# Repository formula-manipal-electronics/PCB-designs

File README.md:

# PCB-designs
This repository contains all the PCB's designed by the Electronics team for the 2020 season.

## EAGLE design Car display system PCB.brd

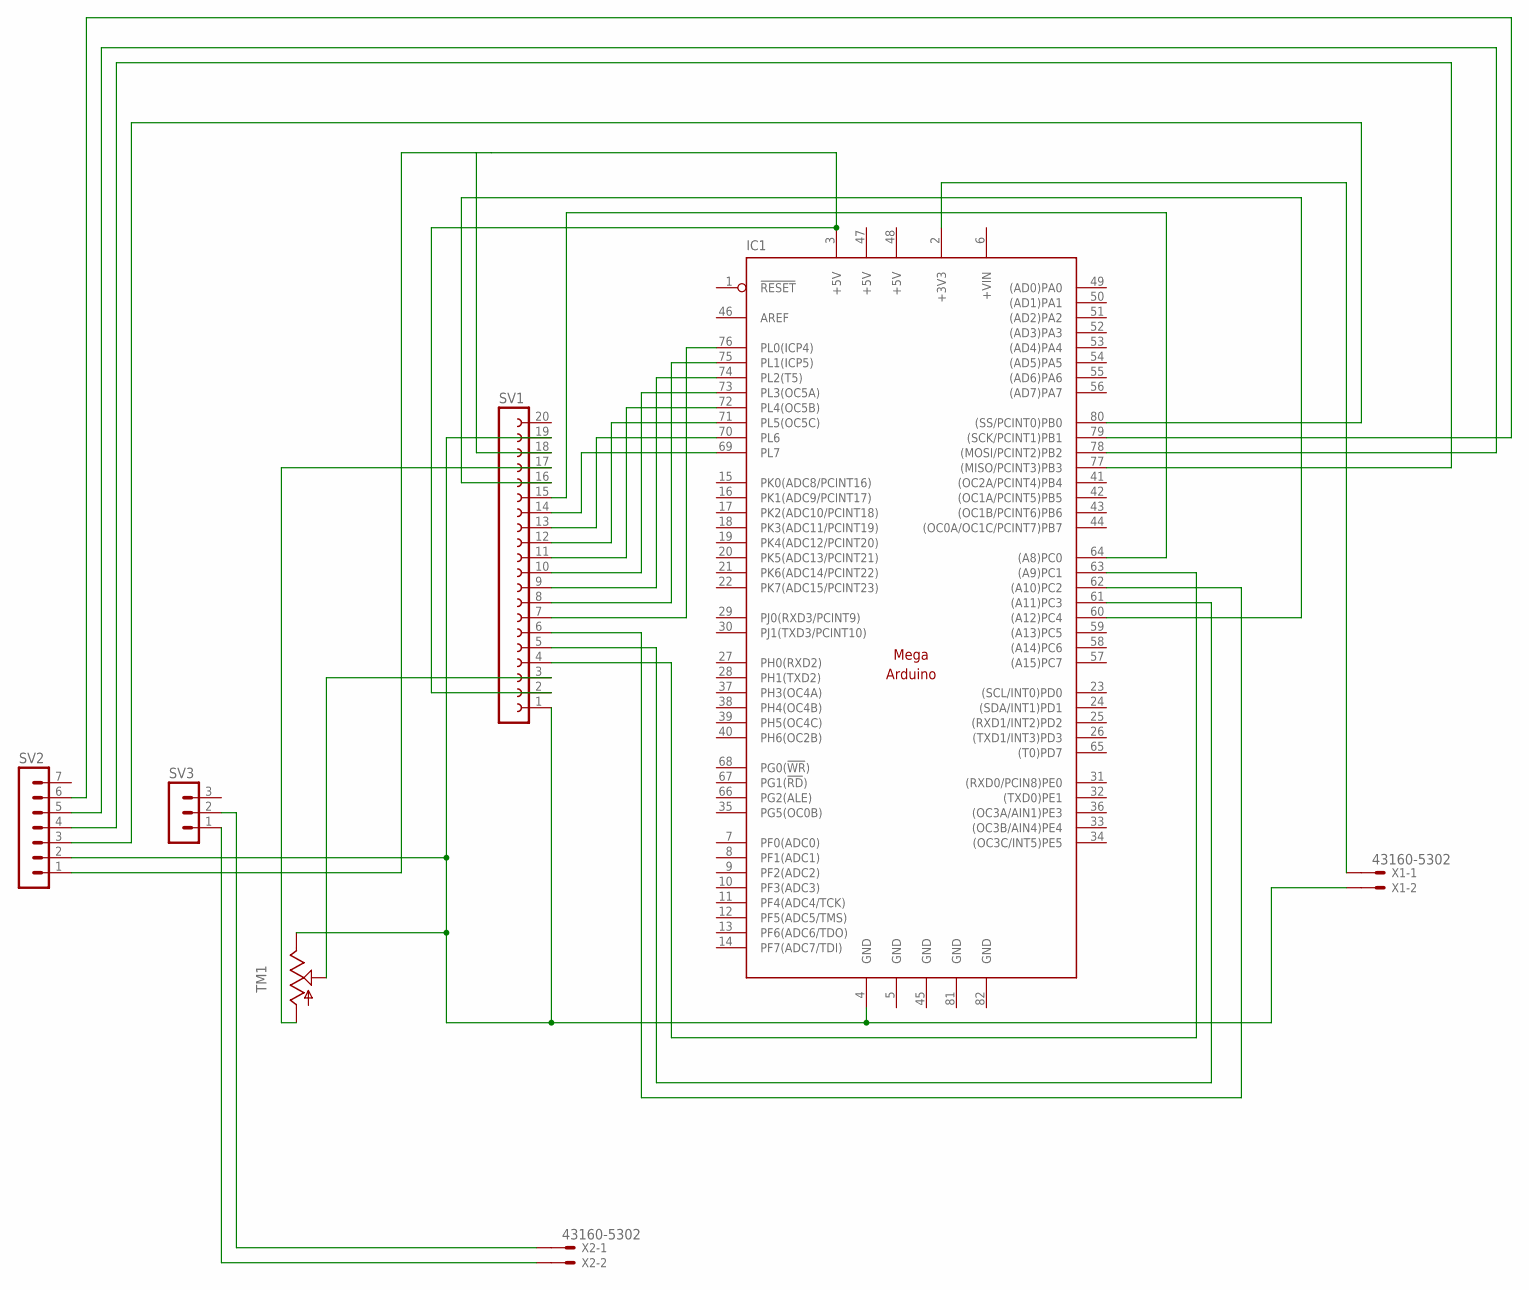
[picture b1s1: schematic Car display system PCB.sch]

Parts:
IC1: MEGAARDUINO_1; MEGA_ARDUINO
SV1: FE20W
SV2: MA07-1
SV3: MA03-1
TM1: TRIM; 6MM
X1, X2: 43160-5302; 43160-XX02

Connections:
+5V: IC1.47 (+5V), IC1.48 (+5V)
+VIN: IC1.6 (+VIN)
GND: IC1.5 (GND), IC1.45 (GND), IC1.81 (GND), IC1.82 (GND)
unnamed: SV1.17, TM1.A
unnamed: IC1.63 ((A9)PC1), SV1.4
unnamed: IC1.61 ((A11)PC3), SV1.5
unnamed: IC1.62 ((A10)PC2), SV1.6
unnamed: IC1.76 (PL0(ICP4)), SV1.7
unnamed: IC1.75 (PL1(ICP5)), SV1.8
unnamed: IC1.74 (PL2(T5)), SV1.9
unnamed: IC1.73 (PL3(OC5A)), SV1.10
unnamed: IC1.72 (PL4(OC5B)), SV1.11
unnamed: IC1.71 (PL5(OC5C)), SV1.12
unnamed: IC1.70 (PL6), SV1.13
unnamed: IC1.69 (PL7), SV1.14
unnamed: IC1.64 ((A8)PC0), SV1.15
unnamed: IC1.60 ((A12)PC4), SV1.16
unnamed: IC1.4 (GND), SV1.1, SV1.19, SV2.2, TM1.E, X1.2@1
unnamed: IC1.3 (+5V), SV1.2, SV1.18, SV2.1
unnamed: IC1.80 ((SS/PCINT0)PB0), SV2.3
unnamed: IC1.77 ((MISO/PCINT3)PB3), SV2.4
unnamed: IC1.78 ((MOSI/PCINT2)PB2), SV2.5
unnamed: IC1.79 ((SCK/PCINT1)PB1), SV2.6
unnamed: SV1.3, TM1.S
unnamed: SV3.1, X2.2@1
unnamed: IC1.2 (+3V3), X1.1@1
unnamed: SV3.2, X2.1@1

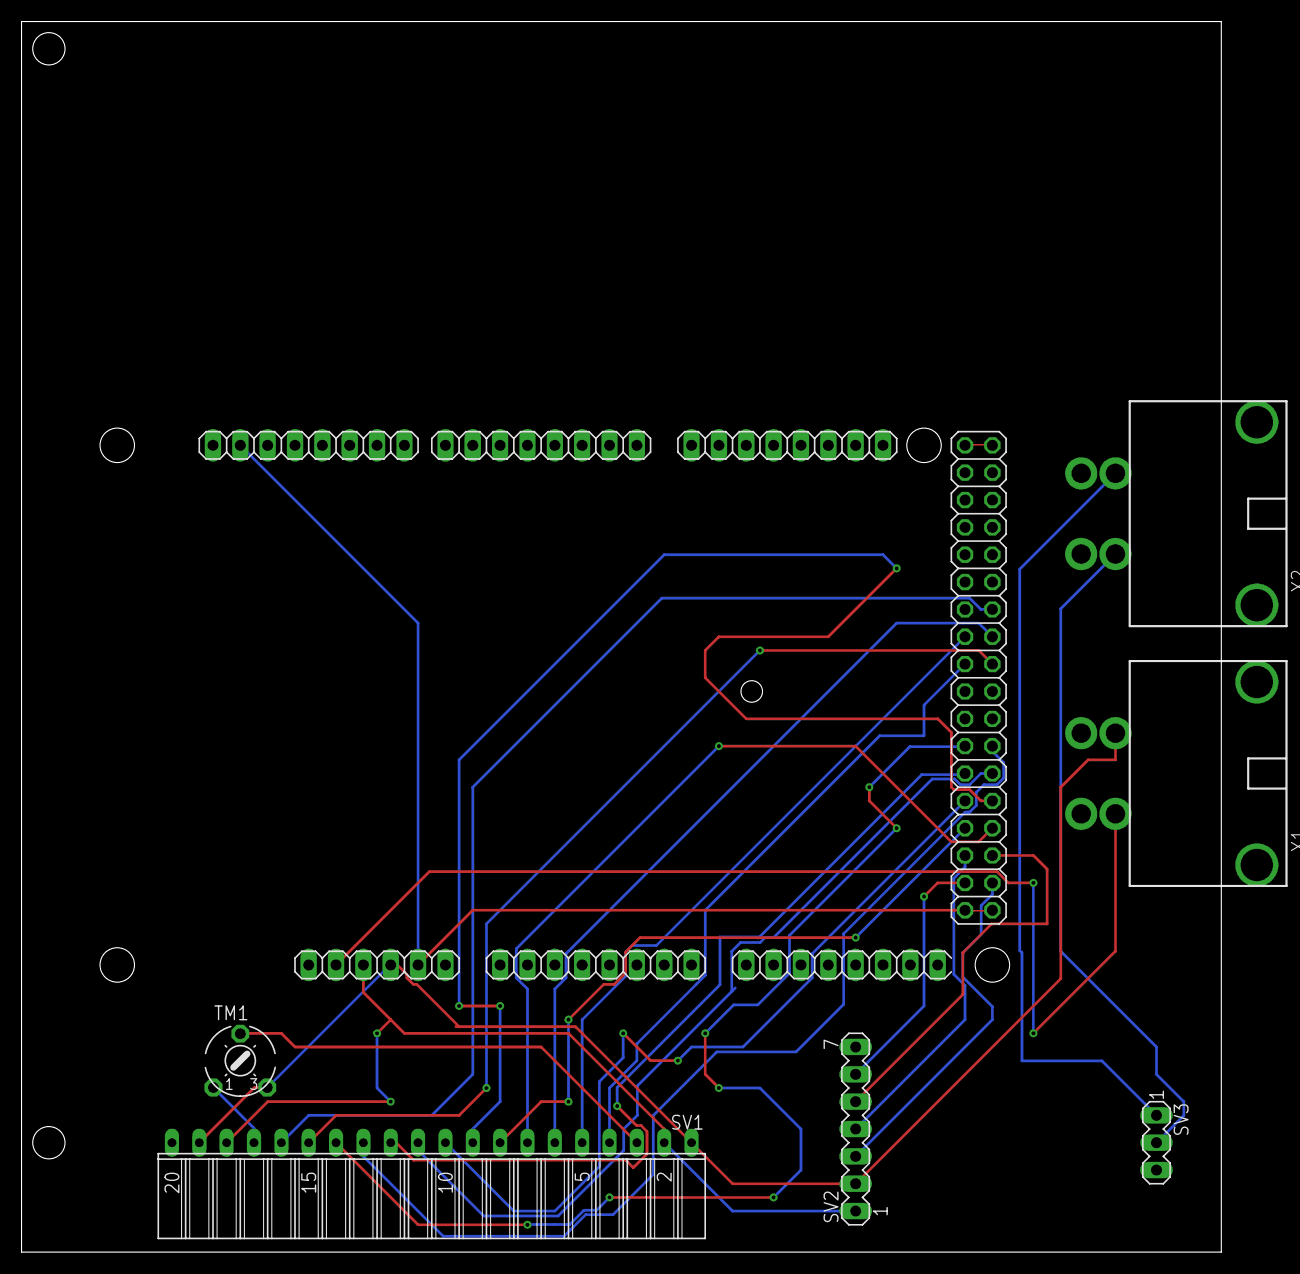
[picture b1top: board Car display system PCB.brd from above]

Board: 2 copper layers, 111.4 x 114.3 mm, 7 parts (0 on the bottom side), 26 nets.

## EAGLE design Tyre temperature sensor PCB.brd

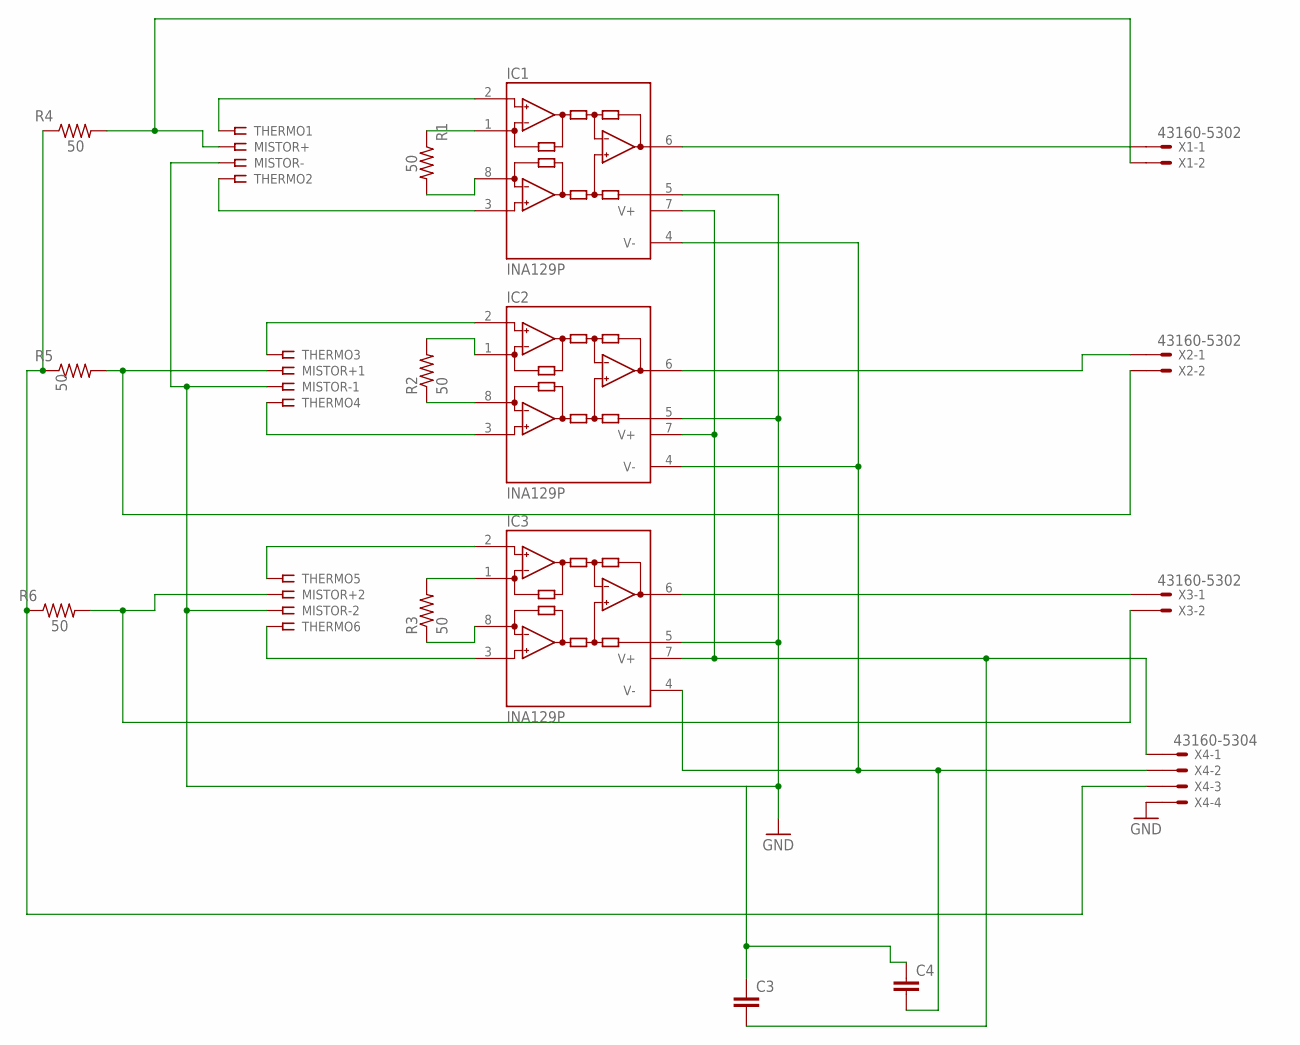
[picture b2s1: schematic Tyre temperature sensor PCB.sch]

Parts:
C3, C4: C5/2.5; C5B2.5
IC1, IC2, IC3: INA129P; DIL08
MISTOR+, MISTOR+1, MISTOR+2: SSW-101-02-G-S
MISTOR-, MISTOR-1, MISTOR-2: SSW-101-02-G-S
R1, R2, R3, R4, R5, R6: 50; 0204/5
THERMO1, THERMO2, THERMO3, THERMO4, THERMO5, THERMO6: SSW-101-02-G-S
X1, X2, X3: 43160-5302; 43160-XX02
X4: 43160-5304; 43160-XX04

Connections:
GND: C3.1, C4.1, IC1.5 (REF), IC2.5 (REF), IC3.5 (REF), MISTOR-.1, MISTOR-1.1, MISTOR-2.1, X4.4@1
unnamed: IC1.1 (RG), R1.1
unnamed: IC1.8 (RG), R1.2
unnamed: IC2.1 (RG), R2.2
unnamed: IC2.8 (RG), R2.1
unnamed: IC3.1 (RG), R3.2
unnamed: IC3.8 (RG), R3.1
unnamed: IC1.3 (+IN), THERMO2.1
unnamed: IC1.2 (-IN), THERMO1.1
unnamed: IC2.3 (+IN), THERMO4.1
unnamed: IC2.2 (-IN), THERMO3.1
unnamed: IC3.3 (+IN), THERMO6.1
unnamed: IC3.2 (-IN), THERMO5.1
unnamed: MISTOR+.1, R4.2, X1.2@1
unnamed: IC1.6 (OUT), X1.1@1
unnamed: IC2.6 (OUT), X2.1@1
unnamed: IC3.6 (OUT), X3.1@1
unnamed: C3.2, IC1.7 (V+), IC2.7 (V+), IC3.7 (V+), X4.1@1
unnamed: C4.2, IC1.4 (V-), IC2.4 (V-), IC3.4 (V-), X4.2@1
unnamed: MISTOR+1.1, R5.2, X2.2@1
unnamed: MISTOR+2.1, R6.2, X3.2@1
unnamed: R4.1, R5.1, R6.1, X4.3@1

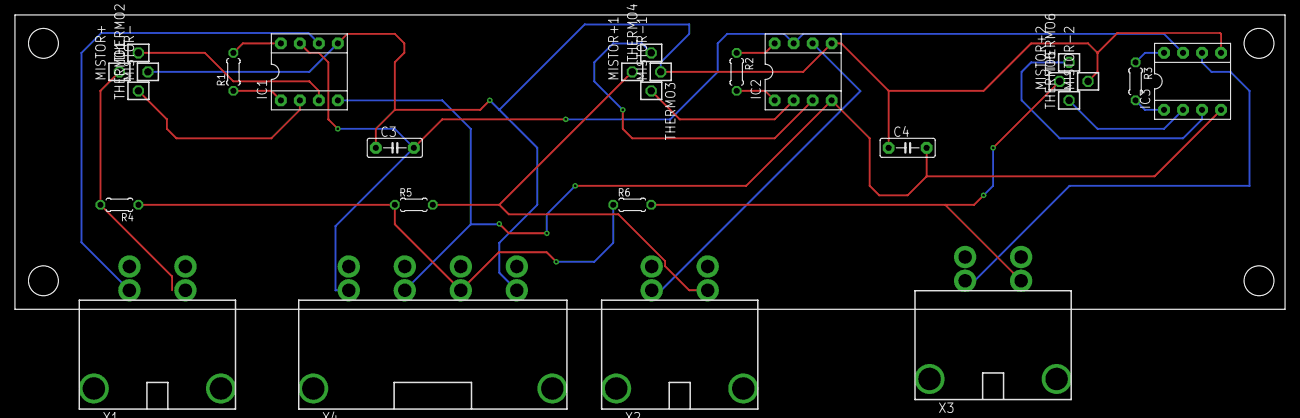
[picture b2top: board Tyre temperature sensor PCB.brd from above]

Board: 2 copper layers, 169.8 x 39.4 mm, 27 parts (0 on the bottom side), 22 nets.

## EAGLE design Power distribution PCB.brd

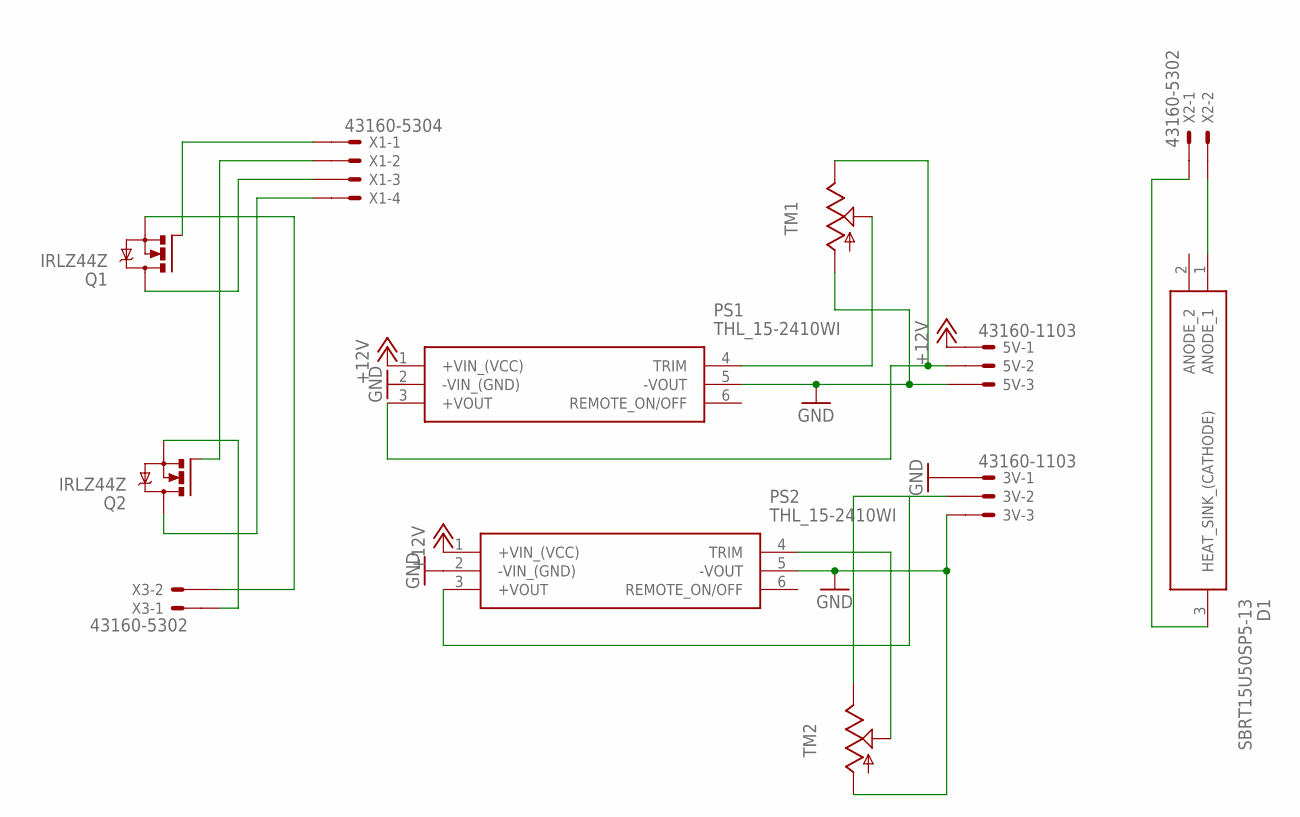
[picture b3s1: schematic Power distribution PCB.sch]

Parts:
3V, 5V: 43160-1103; 43160-XX03
D1: SBRT15U50SP5-13; POWERDI5
PS1, PS2: THL_15-2410WI; THL152410WI
Q1, Q2: IRLZ44Z; TO220BH
TM1, TM2: TRIM; 6MM
X1: 43160-5304; 43160-XX04
X2, X3: 43160-5302; 43160-XX02

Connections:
+12V: 5V.1@1, PS1.1 (+VIN_(VCC)), PS2.1 (+VIN_(VCC))
GND: 3V.1@1, 3V.3@1, 5V.3@1, PS1.5 (-VOUT), PS2.2 (-VIN_(GND)), PS2.5 (-VOUT), TM1.A, TM2.A
unnamed: 5V.2@1, PS1.3 (+VOUT), TM1.E
unnamed: Q1.G, X1.1@1
unnamed: 3V.2@1, PS2.3 (+VOUT), TM2.E
unnamed: Q1.S, X3.2@1
unnamed: PS1.4 (TRIM), TM1.S
unnamed: Q2.S, X3.1@1
unnamed: PS2.4 (TRIM), TM2.S
unnamed: Q2.G, X1.2@1
unnamed: Q1.D, X1.3@1
unnamed: Q2.D, X1.4@1
unnamed: D1.1 (ANODE_1), X2.2@1
unnamed: D1.3 (HEAT_SINK_(CATHODE)), X2.1@1

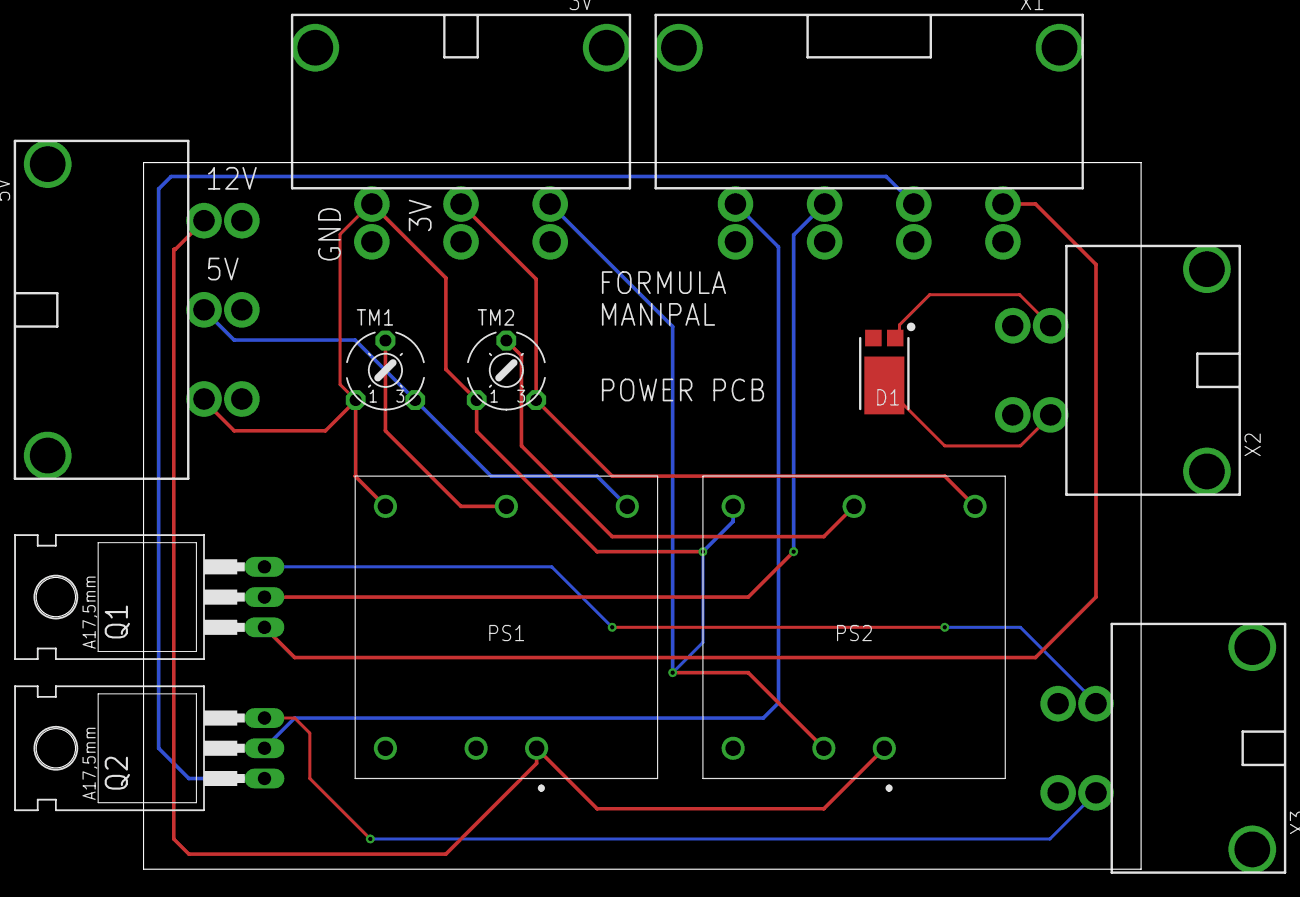
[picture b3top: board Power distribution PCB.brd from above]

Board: 2 copper layers, 83.8 x 59.4 mm, 12 parts (0 on the bottom side), 14 nets.

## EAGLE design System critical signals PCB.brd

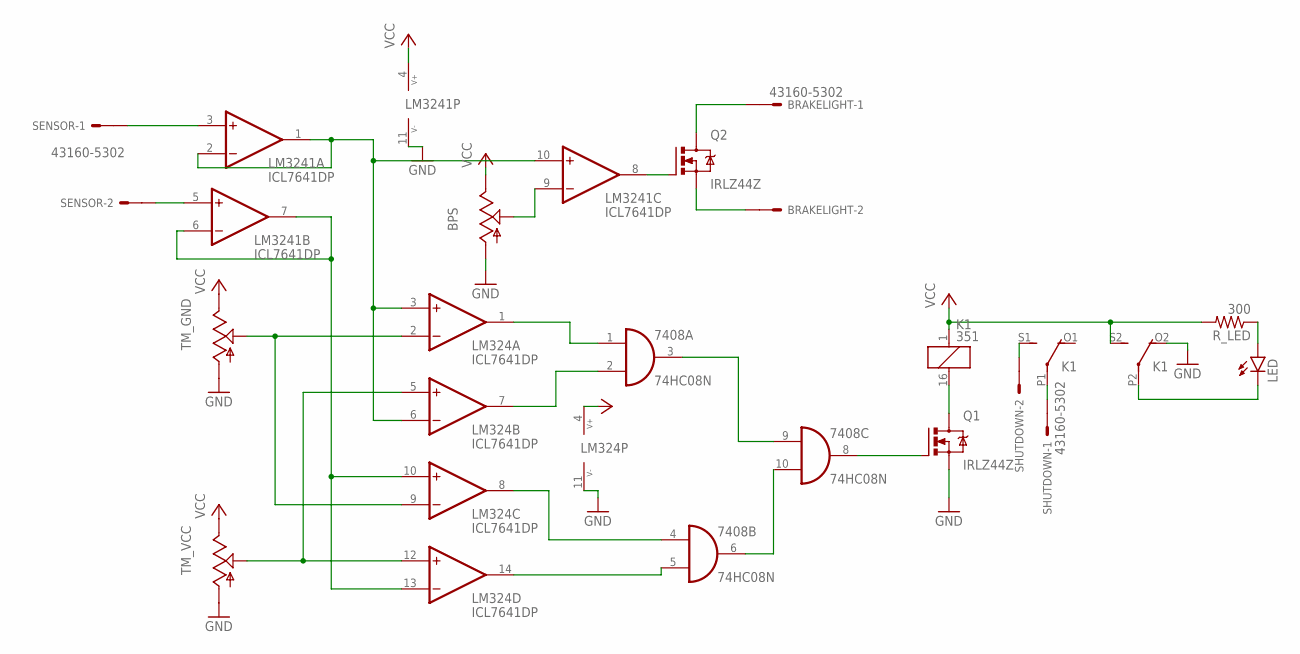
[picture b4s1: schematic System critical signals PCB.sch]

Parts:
7408: 74HC08N; DIL14
BPS: TRIM; 6MM
BRAKELIGHT: 43160-5302; 43160-XX02
K1: 351
LED: LEDCHIP-LED0805; CHIP-LED0805
LM324, LM3241: ICL7641DP; DIL14
Q1, Q2: IRLZ44Z; TO220BH
R_LED: 300; M0805
SENSOR: 43160-5302; 43160-XX02
SHUTDOWN: 43160-5302; 43160-XX02
TM_GND: TRIM; 6MM
TM_VCC: TRIM; 6MM

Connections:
BPS: LM3241.3 (+IN), SENSOR.1@1
GND: 7408.7 (GND), BPS.A, K1.O2 (O), LM324.11 (V-), LM3241.11 (V-), Q1.S, TM_GND.A, TM_VCC.A
unnamed: 7408.4 (I0), LM324.8 (OUT)
unnamed: LM324.3 (+IN), LM324.6 (-IN), LM3241.1 (OUT), LM3241.2 (-IN), LM3241.10 (+IN)
unnamed: LM324.10 (+IN), LM324.13 (-IN), LM3241.6 (-IN), LM3241.7 (OUT)
unnamed: 7408.5 (I1), LM324.14 (OUT)
unnamed: 7408.1 (I0), LM324.1 (OUT)
unnamed: 7408.2 (I1), LM324.7 (OUT)
unnamed: 7408.3 (O), 7408.9 (I0)
unnamed: 7408.6 (O), 7408.10 (I1)
unnamed: 7408.8 (O), Q1.G
unnamed: K1.16 (2), Q1.D
unnamed: K1.S1 (S), SHUTDOWN.2@1
unnamed: K1.P1, SHUTDOWN.1@1
unnamed: LED.A, R_LED.1
unnamed: BPS.S, LM3241.9 (-IN)
unnamed: LM3241.8 (OUT), Q2.G
unnamed: BRAKELIGHT.1@1, Q2.D
unnamed: BRAKELIGHT.2@1, Q2.S
unnamed: K1.P2, LED.C
unnamed: LM324.2 (-IN), LM324.9 (-IN), TM_GND.S
unnamed: LM324.5 (+IN), LM324.12 (+IN), TM_VCC.S
TPS: LM3241.5 (+IN), SENSOR.2@1
VCC: 7408.14 (VCC), BPS.E, K1.1, K1.S2 (S), LM324.4 (V+), LM3241.4 (V+), R_LED.2, TM_GND.E, TM_VCC.E

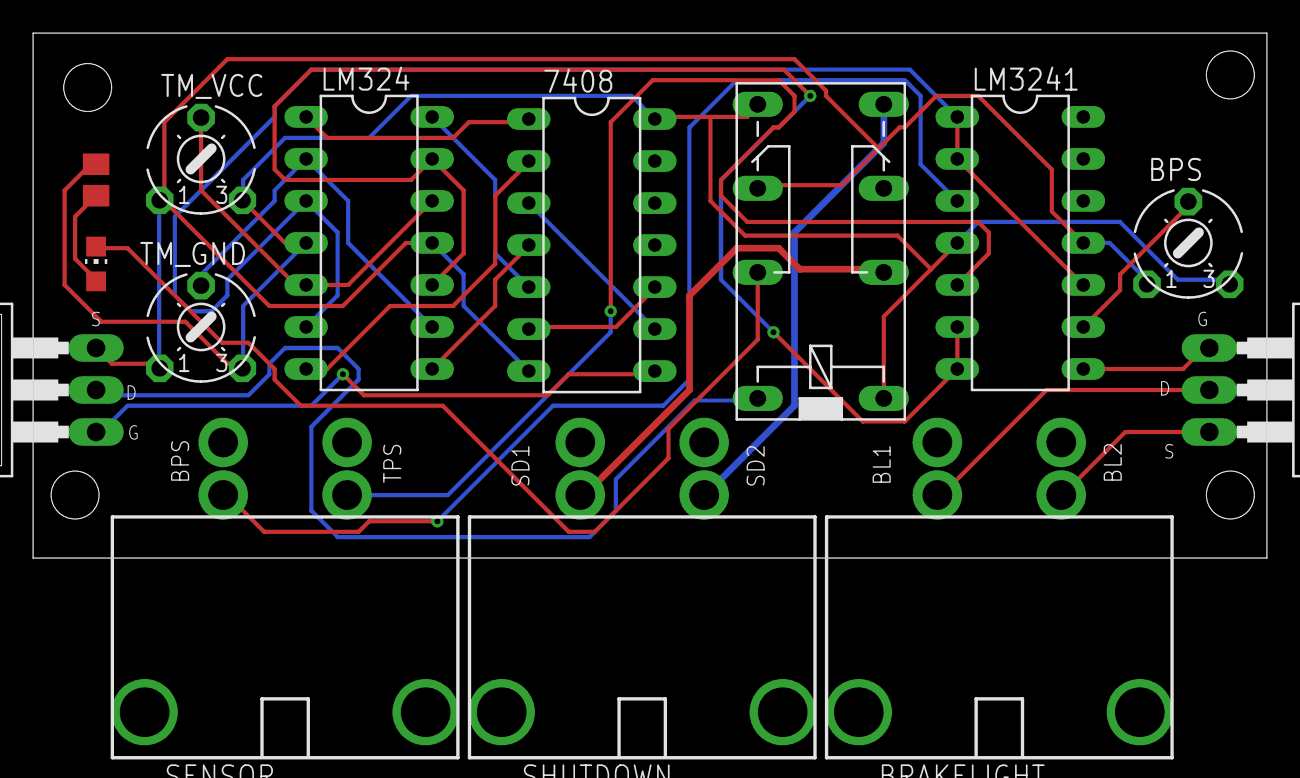
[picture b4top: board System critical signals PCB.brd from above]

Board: 2 copper layers, 74.6 x 31.7 mm, 14 parts (0 on the bottom side), 24 nets.

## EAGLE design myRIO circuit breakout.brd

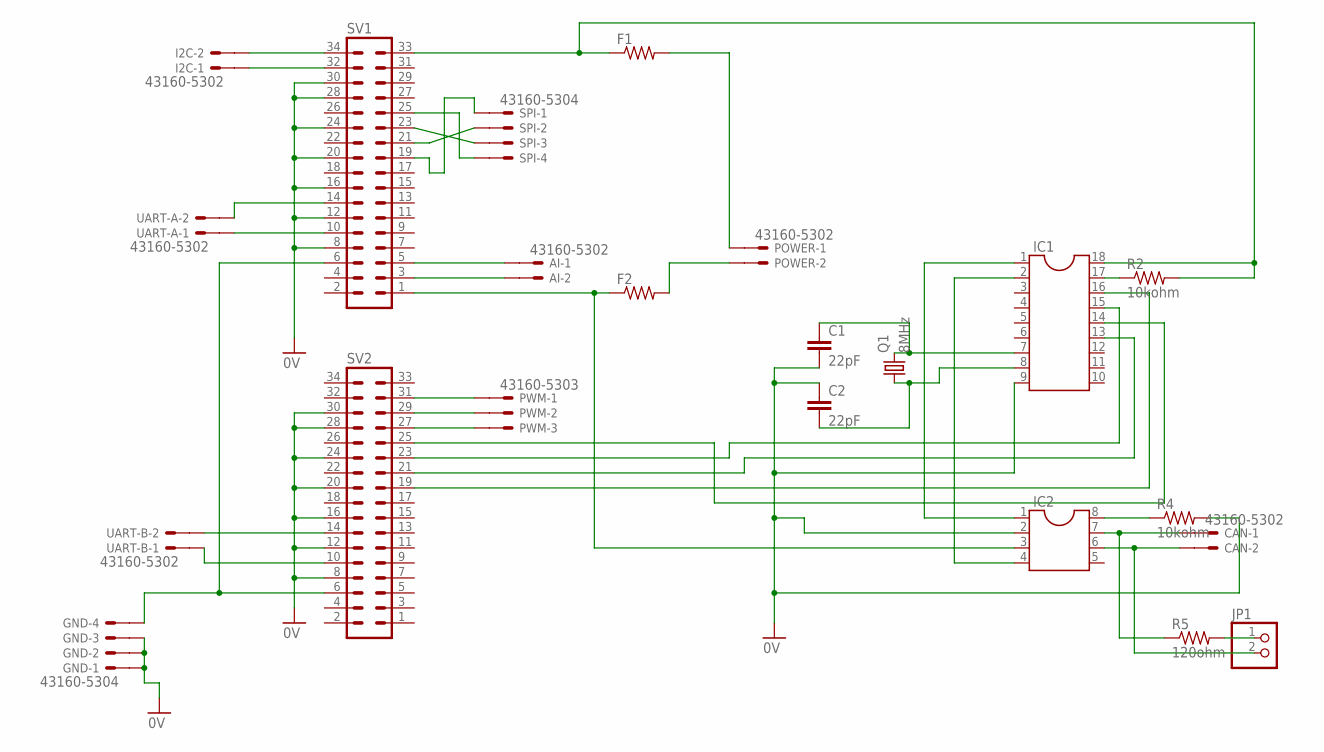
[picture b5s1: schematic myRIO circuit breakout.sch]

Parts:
AI: 43160-5302; 43160-XX02
C1, C2: 22pF; C2.5-3
CAN: 43160-5302; 43160-XX02
F1, F2: R-US_R1206; R1206
GND: 43160-5304; 43160-XX04
I2C: 43160-5302; 43160-XX02
IC1: DIL18
IC2: DIL8; DIL08
JP1: PINHD-1X2; 1X02
POWER: 43160-5302; 43160-XX02
PWM: 43160-5303; 43160-XX03
Q1: 8MHz; HC49/S
R2, R4: 10kohm; 0204/7
R5: 120ohm; 0204/7
SPI: 43160-5304; 43160-XX04
SV1, SV2: MA17-2
UART-A: 43160-5302; 43160-XX02
UART-B: 43160-5302; 43160-XX02

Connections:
0V: C1.2, C2.1, GND.1@1, GND.2@1, GND.3@1, IC1.9, IC2.2, R4.2, SV1.8, SV1.12, SV1.16, SV1.20, SV1.24, SV1.28, SV1.30, SV2.8, SV2.12, SV2.16, SV2.20, SV2.24, SV2.28, SV2.30
unnamed: I2C.2@1, SV1.34
unnamed: I2C.1@1, SV1.32
unnamed: SPI.4@1, SV1.25
unnamed: SPI.2@1, SV1.21
unnamed: SPI.3@1, SV1.23
unnamed: SPI.1@1, SV1.19
unnamed: AI.2@1, SV1.3
unnamed: AI.1@1, SV1.5
unnamed: JP1.1, R5.2
unnamed: SV1.10, UART-A.1@1
unnamed: SV1.14, UART-A.2@1
unnamed: SV2.10, UART-B.1@1
unnamed: SV2.14, UART-B.2@1
unnamed: GND.4@1, SV1.6, SV2.6
unnamed: IC1.1, IC2.1
unnamed: IC1.2, IC2.4
unnamed: C1.1, IC1.7, Q1.2
unnamed: PWM.1@1, SV2.31
unnamed: PWM.2@1, SV2.29
unnamed: PWM.3@1, SV2.27
unnamed: F1.1, IC1.18, R2.2, SV1.33
unnamed: F1.2, POWER.1@1
unnamed: F2.1, IC2.3, SV1.1
unnamed: F2.2, POWER.2@1
unnamed: C2.2, IC1.8, Q1.1
unnamed: IC1.17, R2.1
unnamed: IC1.16, SV2.19
unnamed: IC1.13, SV2.21
unnamed: IC1.15, SV2.23
unnamed: IC1.14, SV2.25
unnamed: IC2.8, R4.1
unnamed: CAN.1@1, IC2.7, R5.1
unnamed: CAN.2@1, IC2.6, JP1.2

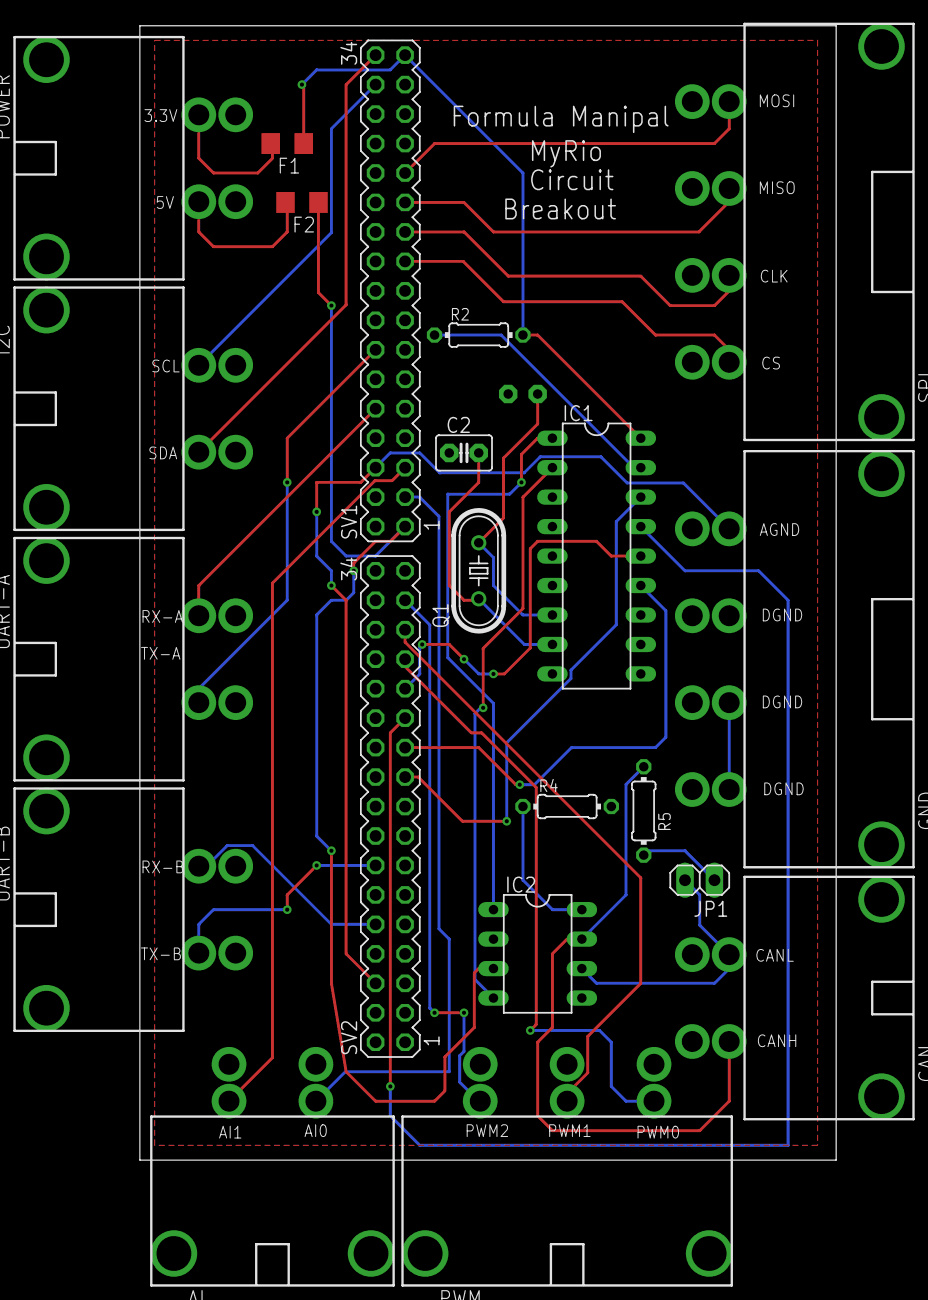
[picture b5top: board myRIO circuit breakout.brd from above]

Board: 2 copper layers, 60.0 x 97.8 mm, 22 parts (1 on the bottom side), 34 nets.
